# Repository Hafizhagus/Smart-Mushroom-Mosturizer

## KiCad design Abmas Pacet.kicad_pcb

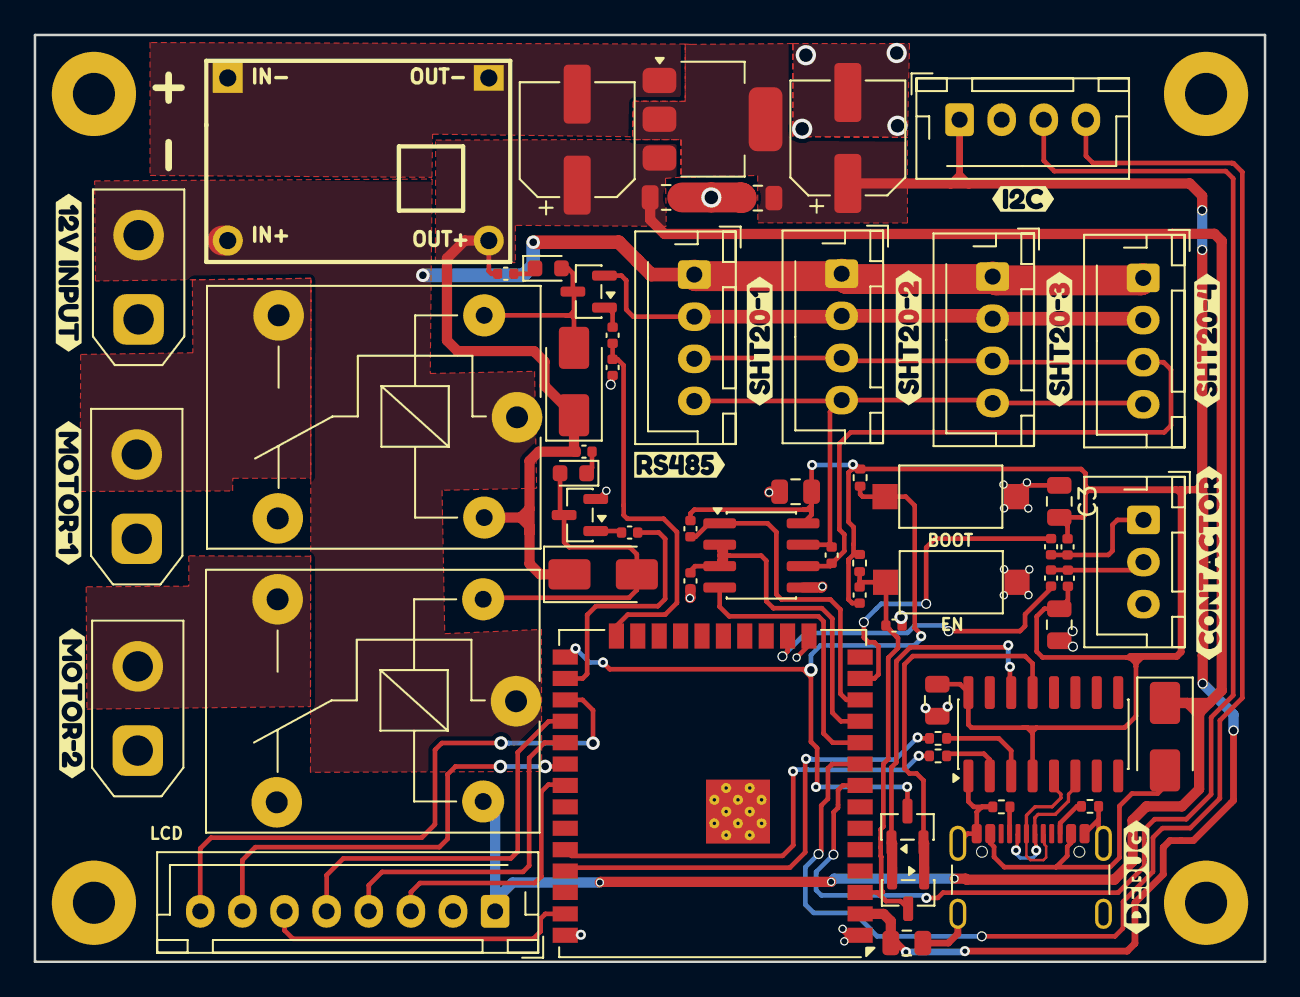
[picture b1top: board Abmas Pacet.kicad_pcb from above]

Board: 2 copper layers, 73.0 x 55.0 mm, 73 parts (0 on the bottom side), 44 nets.

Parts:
C1, C2, C3, C4, C5, C7, C9: 100n; C_0805_2012Metric
C6, C8: 100uF; CP_Elec_6.3x7.7
C10: 1u; C_0402_1005Metric
CN1, CN5, CN6: XT30UPB-M; AMASS_XT30UPB-M_1x02_P5.0mm_Vertical
CN2: CONTACTOR; JST_XH_B3B-XH-AM_1x03_P2.50mm_Vertical
CN4: LCD; JST_XH_B8B-XH-AM_1x08_P2.50mm_Vertical
D1, D4: Z1SMAxxx; D_SMA
D3: SS14; D_SMA
H1, H2, H3, H4: MountingHole_Pad; MountingHole_2.5mm_Pad
J5: USB_C_Receptacle_USB2.0_16P; USB_C_Receptacle_GCT_USB4105-xx-A_16P_TopMnt_Horizontal
K1, K2: SANYOU_SRD_Form_C; Relay_SPDT_SANYOU_SRD_Series_Form_C
LED1, LED2: LED-0603_R; LED_0603_1608Metric
Q1, Q3: MMBT2222A; SOT-23
Q5, Q6: BSS138; SOT-23
R1, R2, R3, R4, R8, R9, R11, R12: 1k; C_0402_1005Metric
R5, R6, R10, R13: 10k; C_0402_1005Metric
R7: 120; C_0402_1005Metric
R15, R89: 5k1; R_0402_1005Metric
R16, R17: 10k; R_0402_1005Metric
R86: 0; R_0402_1005Metric
R87: 0k; R_0402_1005Metric
SW1, SW2: SW_Push; SW_SPST_CK_RS282G05A3
U1: AMS1117-3.3; SOT-223-3_TabPin2
U2: ESP32-WROOM-32UE-N8; ESP32-WROOM-32UE
U3: RS485-4; JST_XH_B4B-XH-AM_1x04_P2.50mm_Vertical
U4: RS485-3; JST_XH_B4B-XH-AM_1x04_P2.50mm_Vertical
U5: CH340C; SOIC-16_3.9x9.9mm_P1.27mm
U6: RS485-2; JST_XH_B4B-XH-AM_1x04_P2.50mm_Vertical
U7: I2C; JST_XH_B4B-XH-AM_1x04_P2.50mm_Vertical
U8: RS485-1; JST_XH_B4B-XH-AM_1x04_P2.50mm_Vertical
U9: MAX3485AEASA+; SOIC-8_3.9x4.9mm_P1.27mm
U10: DC-DC-MINI 360; MINI360 DC ADJUSTABLE POWER SUPPLY BUCK MODULE STEP DOWN MO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
kibuzzard-6AD24BB0: G***; kibuzzard-6AD24BB0
kibuzzard-6AD24C0F: G***; kibuzzard-6AD24C0F
kibuzzard-6AD24C3C: G***; kibuzzard-6AD24C3C
kibuzzard-6AD24C4F: G***; kibuzzard-6AD24C4F
kibuzzard-6AD24C83: G***; kibuzzard-6AD24C83
kibuzzard-6AD24C94: G***; kibuzzard-6AD24C94
kibuzzard-6AD24CAD: G***; kibuzzard-6AD24CAD
kibuzzard-6AD24CC4: G***; kibuzzard-6AD24CC4
kibuzzard-6AD24CF5: G***; kibuzzard-6AD24CF5
kibuzzard-6AD24D1D: G***; kibuzzard-6AD24D1D
kibuzzard-6AD24D45: G***; kibuzzard-6AD24D45

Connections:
+3v3: C1.2, C2.1, C3.2, C4.1, C5.2, C8.1, C9.1, R6.1, R8.1, R12.1, R13.1, R16.1, R17.1, U1.2 (VO), U2.2 (3V3), U5.4 (V3), U5.16 (VCC), U7.1, U9.8 (VCC)
+5v: C6.1, C7.1, CN4.1, D1.1 (K), D3.1 (K), D4.1 (K), K1.5, K2.5, R2.2, R3.2, U1.3 (VI), U10.4 (OUT+)
+12v: CN1.2 (+), K1.1, K2.1, U3.1, U4.1, U6.1, U8.1, U10.3 (IN+)
/A: R7.1, U3.3, U4.3, U6.3, U8.3, U9.6 (A)
/B: R7.2, U3.4, U4.4, U6.4, U8.4, U9.7 (B)
/CH340_D+: J5.A6 (D+), J5.B6 (D+), U5.5 (UD+)
/CH340_D-: J5.A7 (D-), J5.B7 (D-), U5.6 (UD-)
/CS_GPIO5: CN4.3, U2.31 (IO19)
/DCOutput1: CN5.2 (+), K1.3
/DCOutput2: CN6.2 (+), K2.3
/DC_GPIO27: CN4.5, U2.28 (IO17)
/DI_GPIO34: R9.1, U2.13 (IO14)
/DI_GPIO35: R11.1, U2.16 (IO13)
/GPIO4: R5.2, U2.11 (IO26), U9.2 (nRE), U9.3 (DE)
/LED_GPIO32: CN4.8, U2.27 (IO16)
/MOSI_GPIO23: CN4.6, U2.37 (IO23)
/RELAY1_GPIO26: R1.1, U2.26 (IO4)
/RELAY2_GPIO25: R4.1, R10.2, U2.24 (IO2)
/RST_GPIO33: CN4.4, U2.29 (IO5)
/RX0: R86.1, U2.34 (RXD0)
/RX2: R6.2, U2.12 (IO27), U9.1 (RO)
/SCK_GPIO18: CN4.7, U2.30 (IO18)
/SCL_GPIO22: U2.9 (IO33), U7.4
/SDA_GPIO21: U2.8 (IO32), U7.3
/TX0: R87.1, U2.35 (TXD0)
/TX2: U2.10 (IO25), U9.4 (DI)
ESP32_GPIO0: Q6.3 (D), R16.2, SW1.1, U2.25 (IO0)
ESP32_RESET: C10.1, Q5.3 (D), R13.2, R17.2, SW2.1, U2.3 (EN)
GND: C1.1, C2.2, C3.1, C4.2, C5.1, C6.2, C7.2, C8.2, C9.2, C10.2, CN1.1 (-), CN2.3, CN4.2, CN5.1 (-), CN6.1 (-), H1.1, H2.1, H3.1, H4.1, J5.A1 (GND), J5.A12 (GND), J5.B1 (GND), J5.B12 (GND), J5.S1 (SHIELD), Q1.2 (E), Q3.2 (E), R5.1, R10.1, R15.1, R89.1, SW1.2, SW2.2, U1.1 (GND), U2.1 (GND), U2.15 (GND), U2.38 (GND), U2.39 (GND), U3.2, U4.2, U5.1 (GND), U6.2, U7.2, U8.2, U9.5 (GND), U10.1 (GND), U10.2 (GND)
unnamed: CN2.1, R8.2, R9.2
unnamed: CN2.2, R11.2, R12.2
unnamed: D1.2 (A), K2.2, LED2.2, Q1.3 (C)
unnamed: D3.2 (A), J5.A4 (VBUS), J5.A9 (VBUS), J5.B4 (VBUS), J5.B9 (VBUS)
unnamed: D4.2 (A), K1.2, LED1.2, Q3.3 (C)
unnamed: J5.A5 (CC1), R15.2
unnamed: J5.B5 (CC2), R89.2
unnamed: LED1.1, R2.1
unnamed: LED2.1, R3.1
unnamed: Q1.1 (B), R4.2
unnamed: Q3.1 (B), R1.2
unnamed: Q5.1 (G), Q6.2 (S), U5.13 (~DTR)
unnamed: Q5.2 (S), Q6.1 (G), U5.14 (~RTS)
unnamed: R87.2, U5.3 (RXD)
unnamed: R86.2, U5.2 (TXD)
